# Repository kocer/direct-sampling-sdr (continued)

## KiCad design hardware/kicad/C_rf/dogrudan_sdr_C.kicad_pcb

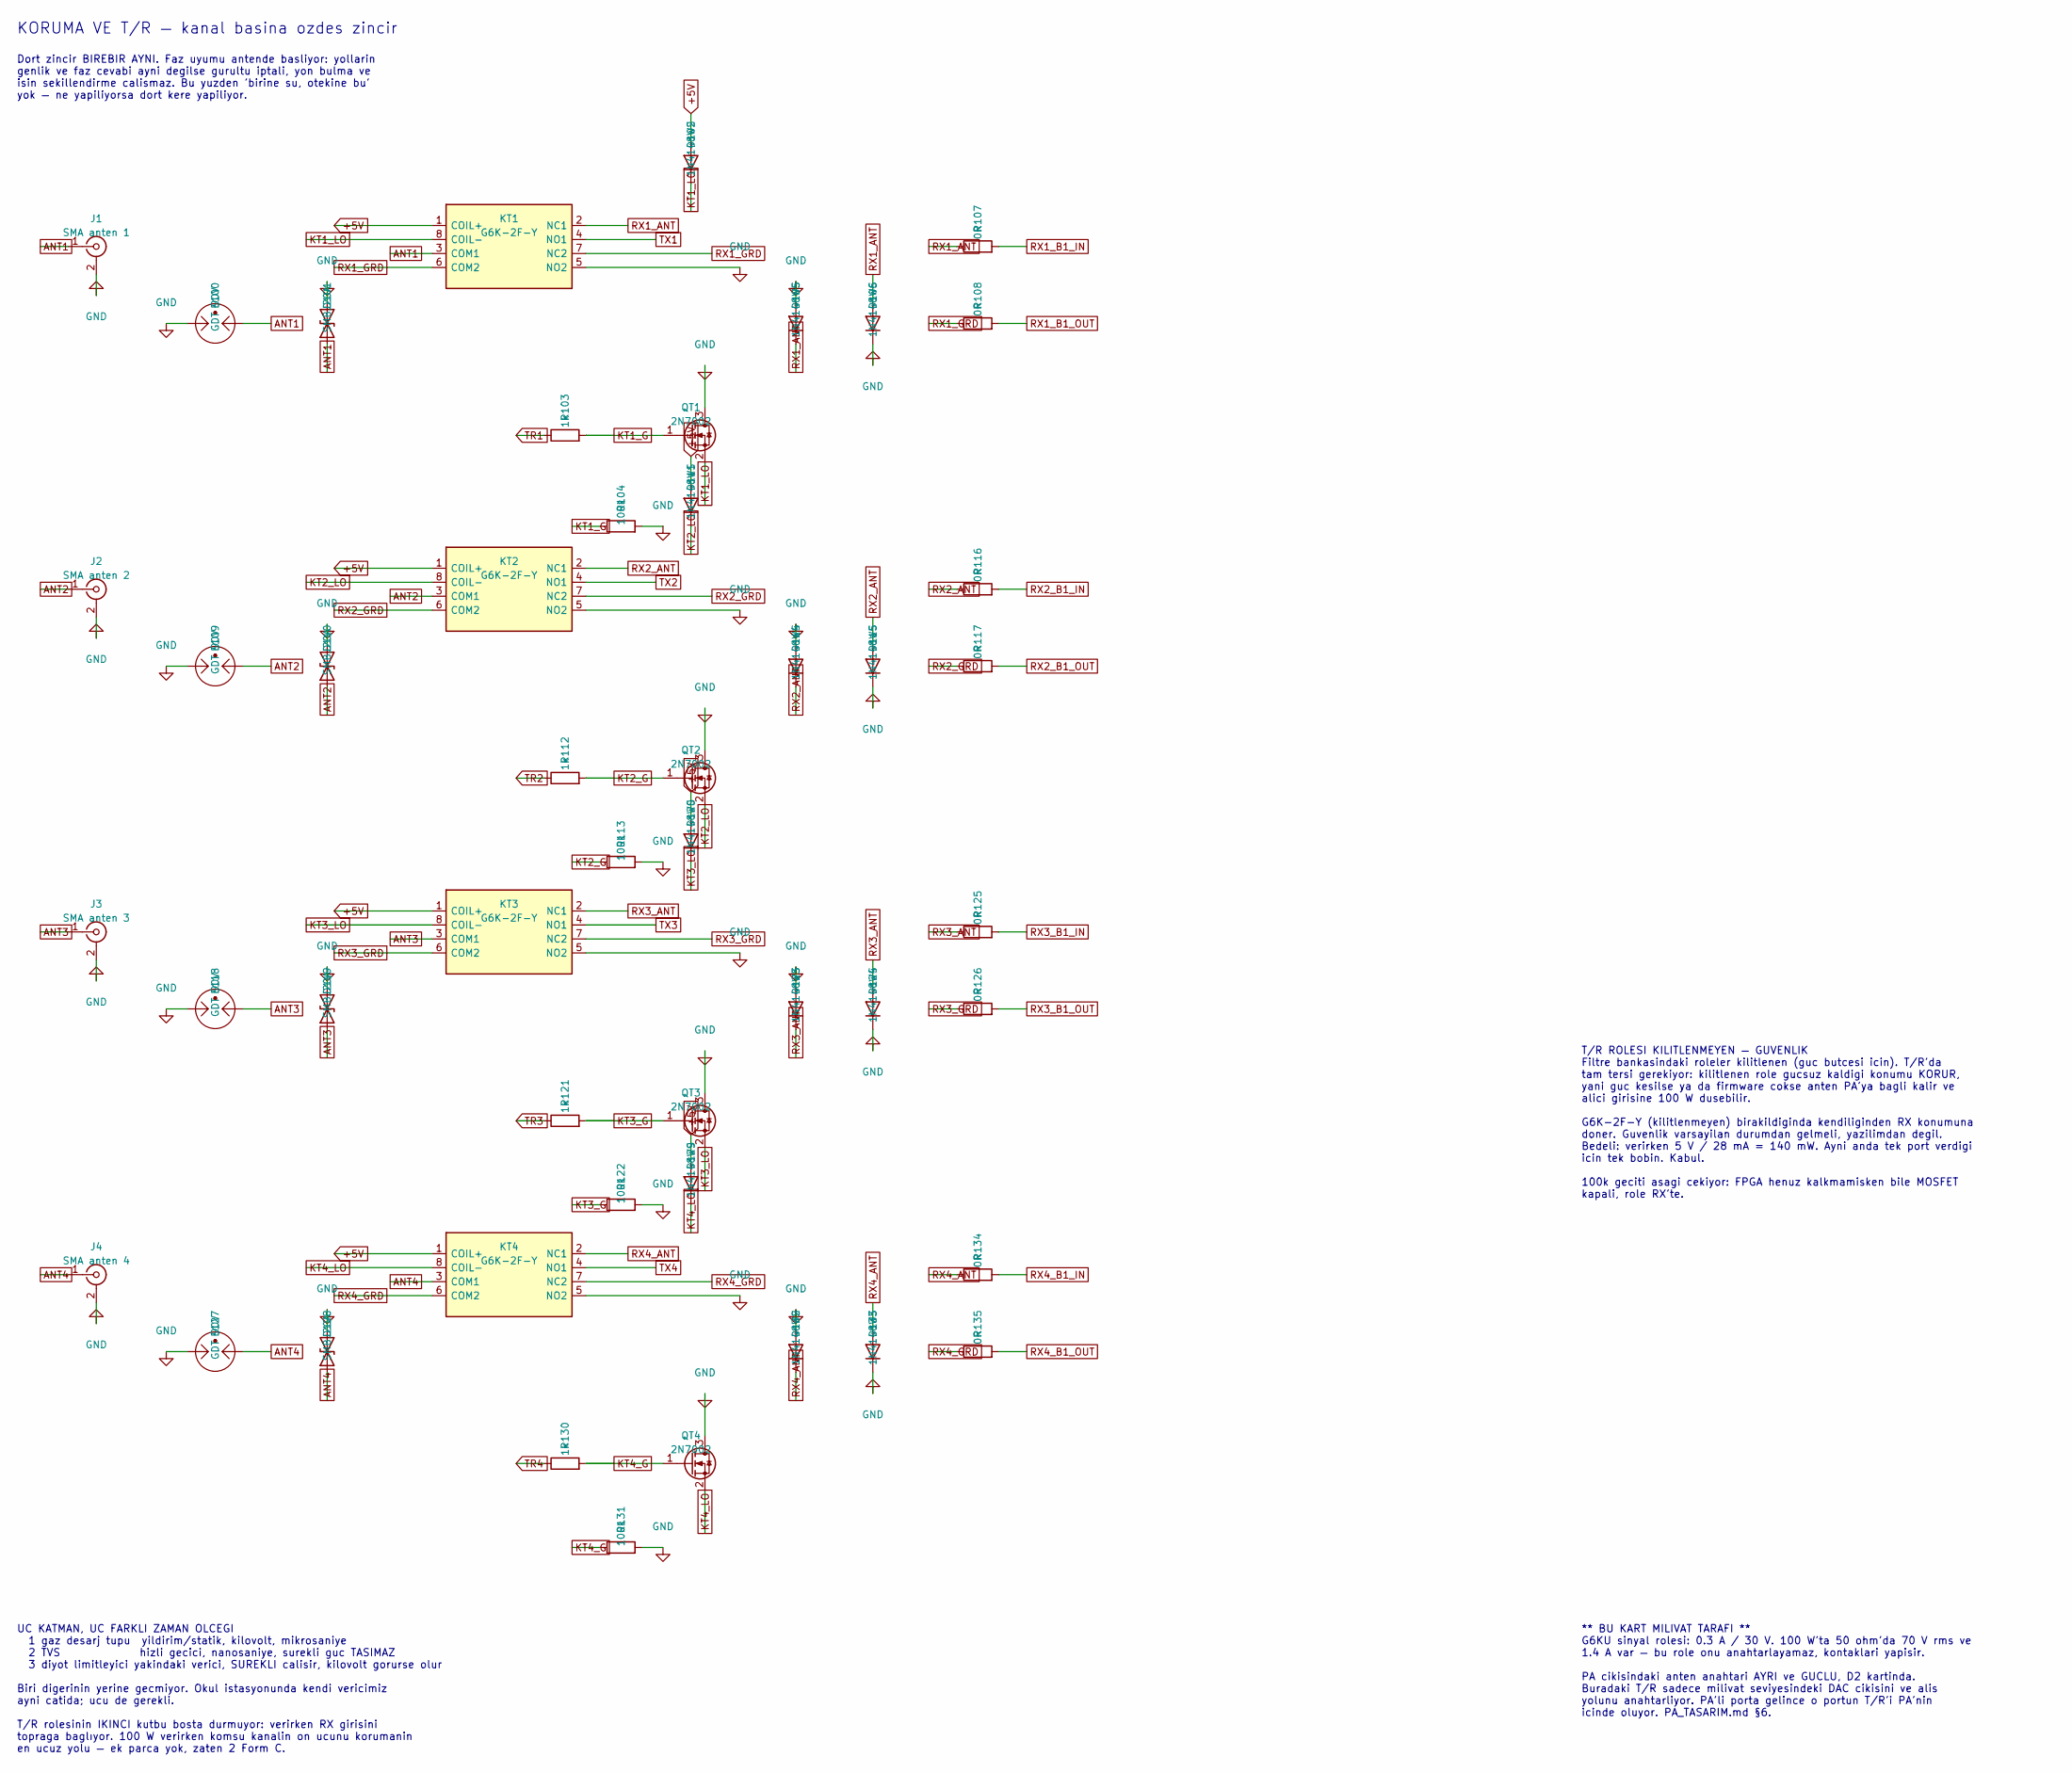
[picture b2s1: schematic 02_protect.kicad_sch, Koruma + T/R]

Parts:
D101, D110, D119, D128: SMBJ20A; D_SMB
D102, D105, D106, D111, D114, D115, D120, D123, D124, D129, D132, D133: 1N4148WS; D_SOD-323
E100, E109, E118, E127: GDT 90V; GDT_Disc_D12mm_W3.9mm_P7.5mm
J1: SMA anten 1; SMA_Amphenol_132289_EdgeMount
J2: SMA anten 2; SMA_Amphenol_132289_EdgeMount
J3: SMA anten 3; SMA_Amphenol_132289_EdgeMount
J4: SMA anten 4; SMA_Amphenol_132289_EdgeMount
KT1, KT2, KT3, KT4: G6K-2F-Y; Relay_DPDT_Omron_G6K-2F-Y
QT1, QT2, QT3, QT4: 2N7002; SOT-23
R103, R112, R121, R130: 1k; R_0603_1608Metric
R104, R113, R122, R131: 100k; R_0603_1608Metric
R107, R108, R116, R117, R125, R126, R134, R135: 0R; R_0603_1608Metric

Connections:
ANT1: D101.1 (A1), E100.1, J1.1 (In), KT1.3 (COM1)
ANT2: D110.1 (A1), E109.1, J2.1 (In), KT2.3 (COM1)
ANT3: D119.1 (A1), E118.1, J3.1 (In), KT3.3 (COM1)
ANT4: D128.1 (A1), E127.1, J4.1 (In), KT4.3 (COM1)
KT1_G: QT1.1 (G), R103.2, R104.1
KT1_LO: D102.1 (K), KT1.8 (COIL-), QT1.2 (S)
KT2_G: QT2.1 (G), R112.2, R113.1
KT2_LO: D111.1 (K), KT2.8 (COIL-), QT2.2 (S)
KT3_G: QT3.1 (G), R121.2, R122.1
KT3_LO: D120.1 (K), KT3.8 (COIL-), QT3.2 (S)
KT4_G: QT4.1 (G), R130.2, R131.1
KT4_LO: D129.1 (K), KT4.8 (COIL-), QT4.2 (S)
RX1_ANT: D105.1 (K), D106.2 (A), KT1.2 (NC1), R107.1
RX1_B1_IN: R107.2; also elsewhere on the board
RX1_B1_OUT: R108.2; also elsewhere on the board
RX1_GRD: KT1.6 (COM2), KT1.7 (NC2), R108.1
RX2_ANT: D114.1 (K), D115.2 (A), KT2.2 (NC1), R116.1
RX2_B1_IN: R116.2; also elsewhere on the board
RX2_B1_OUT: R117.2; also elsewhere on the board
RX2_GRD: KT2.6 (COM2), KT2.7 (NC2), R117.1
RX3_ANT: D123.1 (K), D124.2 (A), KT3.2 (NC1), R125.1
RX3_B1_IN: R125.2; also elsewhere on the board
RX3_B1_OUT: R126.2; also elsewhere on the board
RX3_GRD: KT3.6 (COM2), KT3.7 (NC2), R126.1
RX4_ANT: D132.1 (K), D133.2 (A), KT4.2 (NC1), R134.1
RX4_B1_IN: R134.2; also elsewhere on the board
RX4_B1_OUT: R135.2; also elsewhere on the board
RX4_GRD: KT4.6 (COM2), KT4.7 (NC2), R135.1
TR1: R103.1; also elsewhere on the board
TR2: R112.1; also elsewhere on the board
TR3: R121.1; also elsewhere on the board
TR4: R130.1; also elsewhere on the board
TX1: KT1.4 (NO1); also elsewhere on the board
TX2: KT2.4 (NO1); also elsewhere on the board
TX3: KT3.4 (NO1); also elsewhere on the board
TX4: KT4.4 (NO1); also elsewhere on the board

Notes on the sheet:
UC KATMAN, UC FARKLI ZAMAN OLCEGI 1 gaz desarj tupu yildirim/statik, kilovolt, mikrosaniye 2 TVS hizli gecici, nanosaniye, surekli guc TASIMAZ 3 diyot limitleyici yakindaki verici, SUREKLI calisir, kilovolt gorurse olur Biri digerinin yerine gecmiyor. Okul istasyonunda kendi vericimiz ayni catida; 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
T/R ROLESI KILITLENMEYEN — GUVENLIK Filtre bankasindaki roleler kilitlenen (guc butcesi icin). T/R'da tam tersi gerekiyor: kilitlenen role gucsuz kaldigi konumu KORUR, yani guc kesilse ya da firmware cokse anten PA'ya bagli kalir ve alici girisine 100 W dusebilir. G6K-2F-Y (kilitlenmeyen) birakildi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
** BU KART MILIVAT TARAFI ** G6KU sinyal rolesi: 0.3 A / 30 V. 100 W'ta 50 ohm'da 70 V rms ve 1.4 A var — bu role onu anahtarlayamaz, kontaklari yapisir. PA cikisindaki anten anahtari AYRI ve GUCLU, D2 kartinda. Buradaki T/R sadece milivat seviyesindeki DAC cikisini ve alis yolunu anahtarliyor. PA'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
Dort zincir BIREBIR AYNI. Faz uyumu antende basliyor: yollarin genlik ve faz cevabi ayni degilse gurultu iptali, yon bulma ve isin sekillendirme calismaz. Bu yuzden 'birine su, otekine bu' yok — ne yapiliyorsa dort kere yapiliyor.
KORUMA VE T/R — kanal basina ozdes zincir
